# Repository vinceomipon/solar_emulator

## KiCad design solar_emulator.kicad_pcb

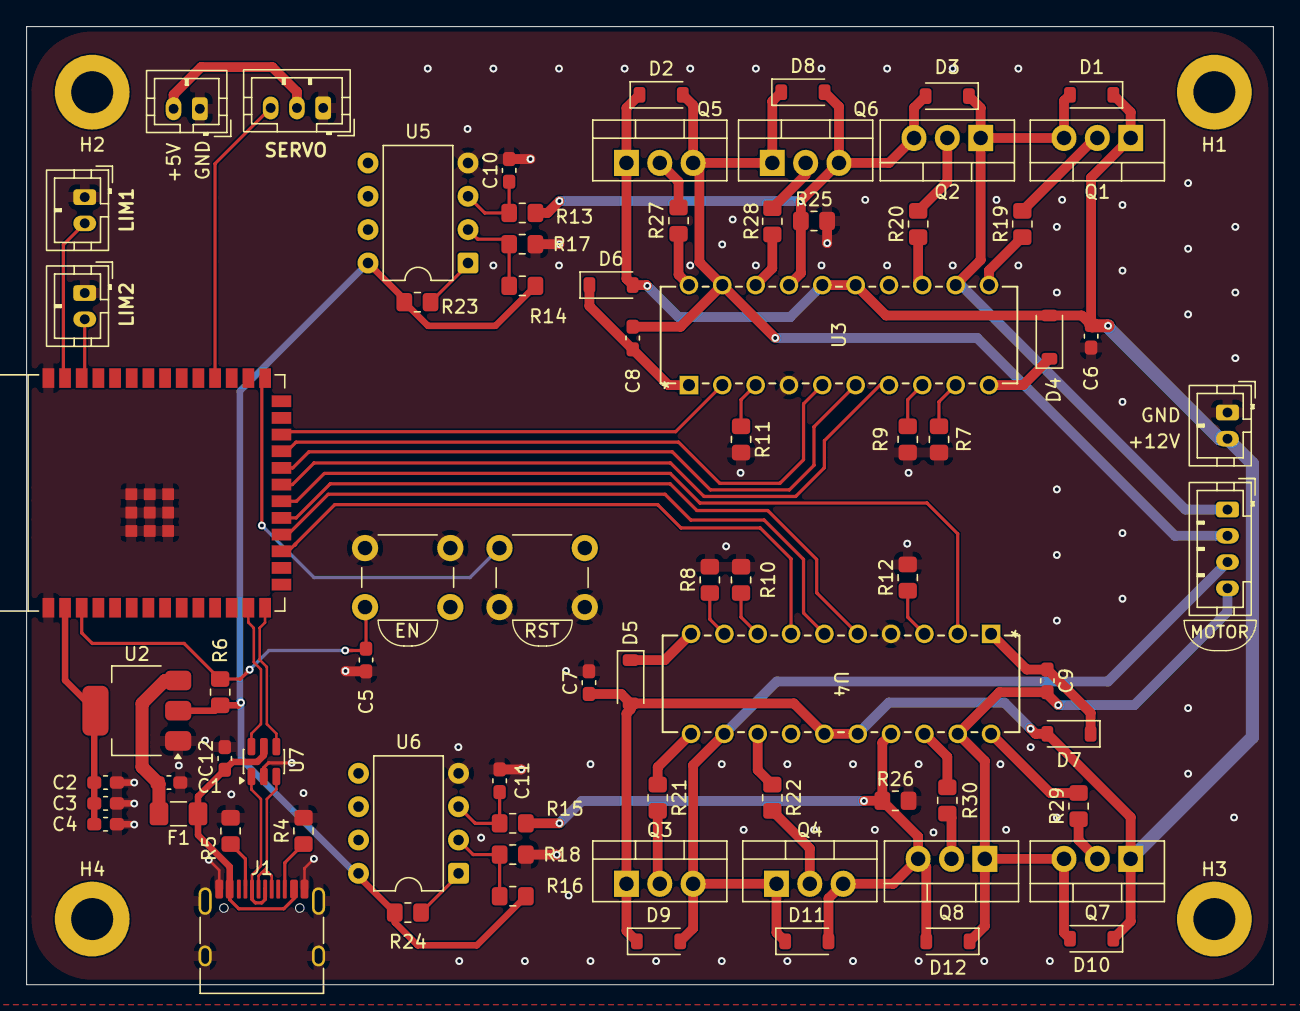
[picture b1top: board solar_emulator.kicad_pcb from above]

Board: 2 copper layers, 95.0 x 73.0 mm, 80 parts (0 on the bottom side), 59 nets.

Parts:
C1, C4: 100n; C_0603_1608Metric_Pad1.08x0.95mm_HandSolder
C2, C12: 10u; C_0603_1608Metric_Pad1.08x0.95mm_HandSolder
C3: 22u; C_0603_1608Metric_Pad1.08x0.95mm_HandSolder
C5, C6, C7, C8, C9: 1u; C_0603_1608Metric_Pad1.08x0.95mm_HandSolder
C10, C11: 1n; C_0603_1608Metric_Pad1.08x0.95mm_HandSolder
D1, D2, D3, D8, D9, D10, D11, D12: D_Zener; D_SOD-123
D4, D5, D6, D7: 1N5819; D_SOD-123
F1: Fuse_Small; Fuse_1206_3216Metric_Pad1.42x1.75mm_HandSolder
H1, H2, H3, H4: MountingHole; MountingHole_3.2mm_M3_ISO7380_Pad
J1: USB_C_Receptacle_USB2.0_16P; USB_C_Receptacle_HRO_TYPE-C-31-M-12
J2, J3, J4, J5: Conn_01x02; JST_PH_B2B-PH-K_1x02_P2.00mm_Vertical
J6: Conn_01x03; JST_PH_B3B-PH-K_1x03_P2.00mm_Vertical
J7: Conn_01x04; JST_PH_B4B-PH-K_1x04_P2.00mm_Vertical
Q1, Q2, Q3, Q4, Q5, Q6, Q7, Q8: IRFZ44N; TO-220-3_Vertical
R4, R5: 5.1k; R_0805_2012Metric_Pad1.20x1.40mm_HandSolder
R6, R11, R12, R14, R16: 10k; R_0805_2012Metric_Pad1.20x1.40mm_HandSolder
R7, R8, R9, R10: 22k; R_0805_2012Metric_Pad1.20x1.40mm_HandSolder
R13, R15: 1k; R_0805_2012Metric_Pad1.20x1.40mm_HandSolder
R17, R18: 470; R_0805_2012Metric_Pad1.20x1.40mm_HandSolder
R19, R20, R21, R22, R27, R28, R29, R30: 10; R_0805_2012Metric_Pad1.20x1.40mm_HandSolder
R23, R24: 2.2k; R_0805_2012Metric_Pad1.20x1.40mm_HandSolder
R25, R26: 0.1; R_0805_2012Metric_Pad1.20x1.40mm_HandSolder
SW1, SW2: SW_Push; SW_PUSH_6mm_H4.3mm
U1: ESP32-S3-WROOM-1
U2: LD1117S33TR_SOT223; SOT-223-3_TabPin2
U3, U4: HIP4081AIPZ; PDIP20_7P11X26P9_INR
U5, U6: LM393; DIP-8_W7.62mm
U7: USBLC6-2SC6; SOT-23-6

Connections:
5V: J4.2, J6.2
+3V3: C2.1, C3.1, C4.1, R6.1, R14.1, R16.1, R23.1, R24.1, U1.2 (3V3), U2.2 (VO), U5.8 (V+), U6.8 (V+)
+5V: C1.1, F1.2, U2.3 (VI)
+12V: C6.1, C7.1, D1.1 (K), D2.1 (K), D4.2 (A), D5.2 (A), D6.2 (A), D7.2 (A), D9.1 (K), D10.1 (K), J3.2, Q1.1 (D), Q3.1 (D), Q5.1 (D), Q7.1 (D), U3.15 (VCC), U3.16 (VDD), U4.15 (VCC), U4.16 (VDD)
/Motor Driver 1/DIS1: R11.1, U3.3 (DIS)
/Motor Driver 1/MOTOR1: D1.2 (A), D3.1 (K), Q1.3 (S), Q2.1 (D), U3.12 (AHS)
AHI2: U1.17 (GPIO9/TOUCH9/ADC1_CH8/FSPIHD/SUBSPIHD), U4.7 (AHI)
ALI2: U1.18 (GPIO10/TOUCH10/ADC1_CH9/FSPICS0/FSPIIO4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), U4.6 (ALI)
BHI2: U1.20 (GPIO12/TOUCH12/ADC2_CH1/FSPICLK/FSPIIO6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), U4.2 (BHI)
BHO1: R27.2, U3.20 (BHO)
BHO2: R29.2, U4.20 (BHO)
BHS1: C8.2, D2.2 (A), D8.1 (K), Q5.3 (S), Q6.1 (D), U3.19 (BHS)
BHS2: C9.2, D10.2 (A), D12.1 (K), J7.4, Q7.3 (S), Q8.1 (D), U4.19 (BHS)
BLI2: U1.19 (GPIO11/TOUCH11/ADC2_CH0/FSPID/FSPIIO5/S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), U4.5 (BLI)
BLO1: R28.2, U3.18 (BLO)
BLO2: R30.2, U4.18 (BLO)
BLS1: D3.2 (A), D8.2 (A), Q2.3 (S), Q6.3 (S), R25.1, U3.14 (ALS), U3.17 (BLS)
BLS2: D11.2 (A), D12.2 (A), Q4.3 (S), Q8.3 (S), R15.1, R26.1, U4.14 (ALS), U4.17 (BLS)
D+: J1.A6 (D+), J1.B6 (D+), U7.3 (I/O2)
D-: J1.A7 (D-), J1.B7 (D-), U7.1 (I/O1)
DIS2: R12.1, U4.3 (DIS)
EN: C5.1, R6.2, SW2.1, U1.3 (EN)
GND: C1.2, C2.2, C3.2, C4.2, C5.2, C6.2, C7.2, C10.2, C11.2, C12.2, J1.A1 (GND), J1.A12 (GND), J1.B1 (GND), J1.B12 (GND), J1.SH (SHIELD), J2.1, J3.1, J4.1, J5.1, J6.1, R4.2, R5.2, R7.2, R8.2, R9.2, R10.2, R11.2, R12.2, R17.1, R18.1, R25.2, R26.2, SW1.2, SW2.2, U1.1 (GND), U1.40 (GND), U1.41 (GND), U2.1 (GND), U3.4 (VSS), U4.4 (VSS), U5.4 (V-), U6.4 (V-), U7.2 (GND)
GPIO0: SW1.1, U1.27 (GPIO0/BOOT)
LIMIT1: J2.2, U1.39 (GPIO1/TOUCH1/ADC1_CH0)
LIMIT2: J5.2, U1.38 (GPIO2/TOUCH2/ADC1_CH1)
MOTOR3: D9.2 (A), D11.1 (K), J7.3, Q3.3 (S), Q4.1 (D), U4.12 (AHS)
unnamed: D4.1 (K), U3.10 (AHB)
unnamed: D5.1 (K), U4.10 (AHB)
unnamed: C8.1, D6.1 (K), U3.1 (BHB)
unnamed: C9.1, D7.1 (K), U4.1 (BHB)
unnamed: J1.A5 (CC1), R5.1
unnamed: J1.B5 (CC2), R4.1
unnamed: Q1.2 (G), R19.2
unnamed: Q2.2 (G), R20.2
unnamed: Q3.2 (G), R21.2
unnamed: Q4.2 (G), R22.2
unnamed: Q5.2 (G), R27.1
unnamed: Q6.2 (G), R28.1
unnamed: Q7.2 (G), R29.1
unnamed: Q8.2 (G), R30.1
unnamed: R19.1, U3.11 (AHO)
unnamed: R20.1, U3.13 (ALO)
unnamed: R9.1, U3.8 (HDEL)
unnamed: R7.1, U3.9 (LDEL)
unnamed: R21.1, U4.11 (AHO)
unnamed: R22.1, U4.13 (ALO)
unnamed: R10.1, U4.8 (HDEL)
unnamed: R8.1, U4.9 (LDEL)
unnamed: C10.1, R13.2, U5.3 (+)
unnamed: R14.2, R17.2, U5.2 (-)
unnamed: C11.1, R15.2, U6.3 (+)
unnamed: R16.2, R18.2, U6.2 (-)
OCP1: R23.2, U5.1
OCP2: R24.2, U6.1
SERVO: J6.3, U1.30 (SPIDQS/GPIO37/FSPIQ/SUBSPIQ)
USB_D+: U1.14 (GPIO20/U1CTS/ADC2_CH9/CLK_OUT1/USB_D+), U7.4 (I/O2)
USB_D-: U1.13 (GPIO19/U1RTS/ADC2_CH8/CLK_OUT2/USB_D-), U7.6 (I/O1)
VBUS: C12.1, F1.1, J1.A4 (VBUS), J1.A9 (VBUS), J1.B4 (VBUS), J1.B9 (VBUS), U7.5 (VBUS)
